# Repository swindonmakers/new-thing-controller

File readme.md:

Universal WIFI Thing Controller for doing stuff around the makerspace. Machine control, data logging, etc etc.

## Features:
 * Wifi (via Pico W)
 * SPI LCD
 * Resistive touch
 * SD card
 * Buttons
 * WS2812B (onboard + header)
 * 2x relay/contactor coil outputs
 * PN532 NFC card reader header
 * Unusued GPIO expansion

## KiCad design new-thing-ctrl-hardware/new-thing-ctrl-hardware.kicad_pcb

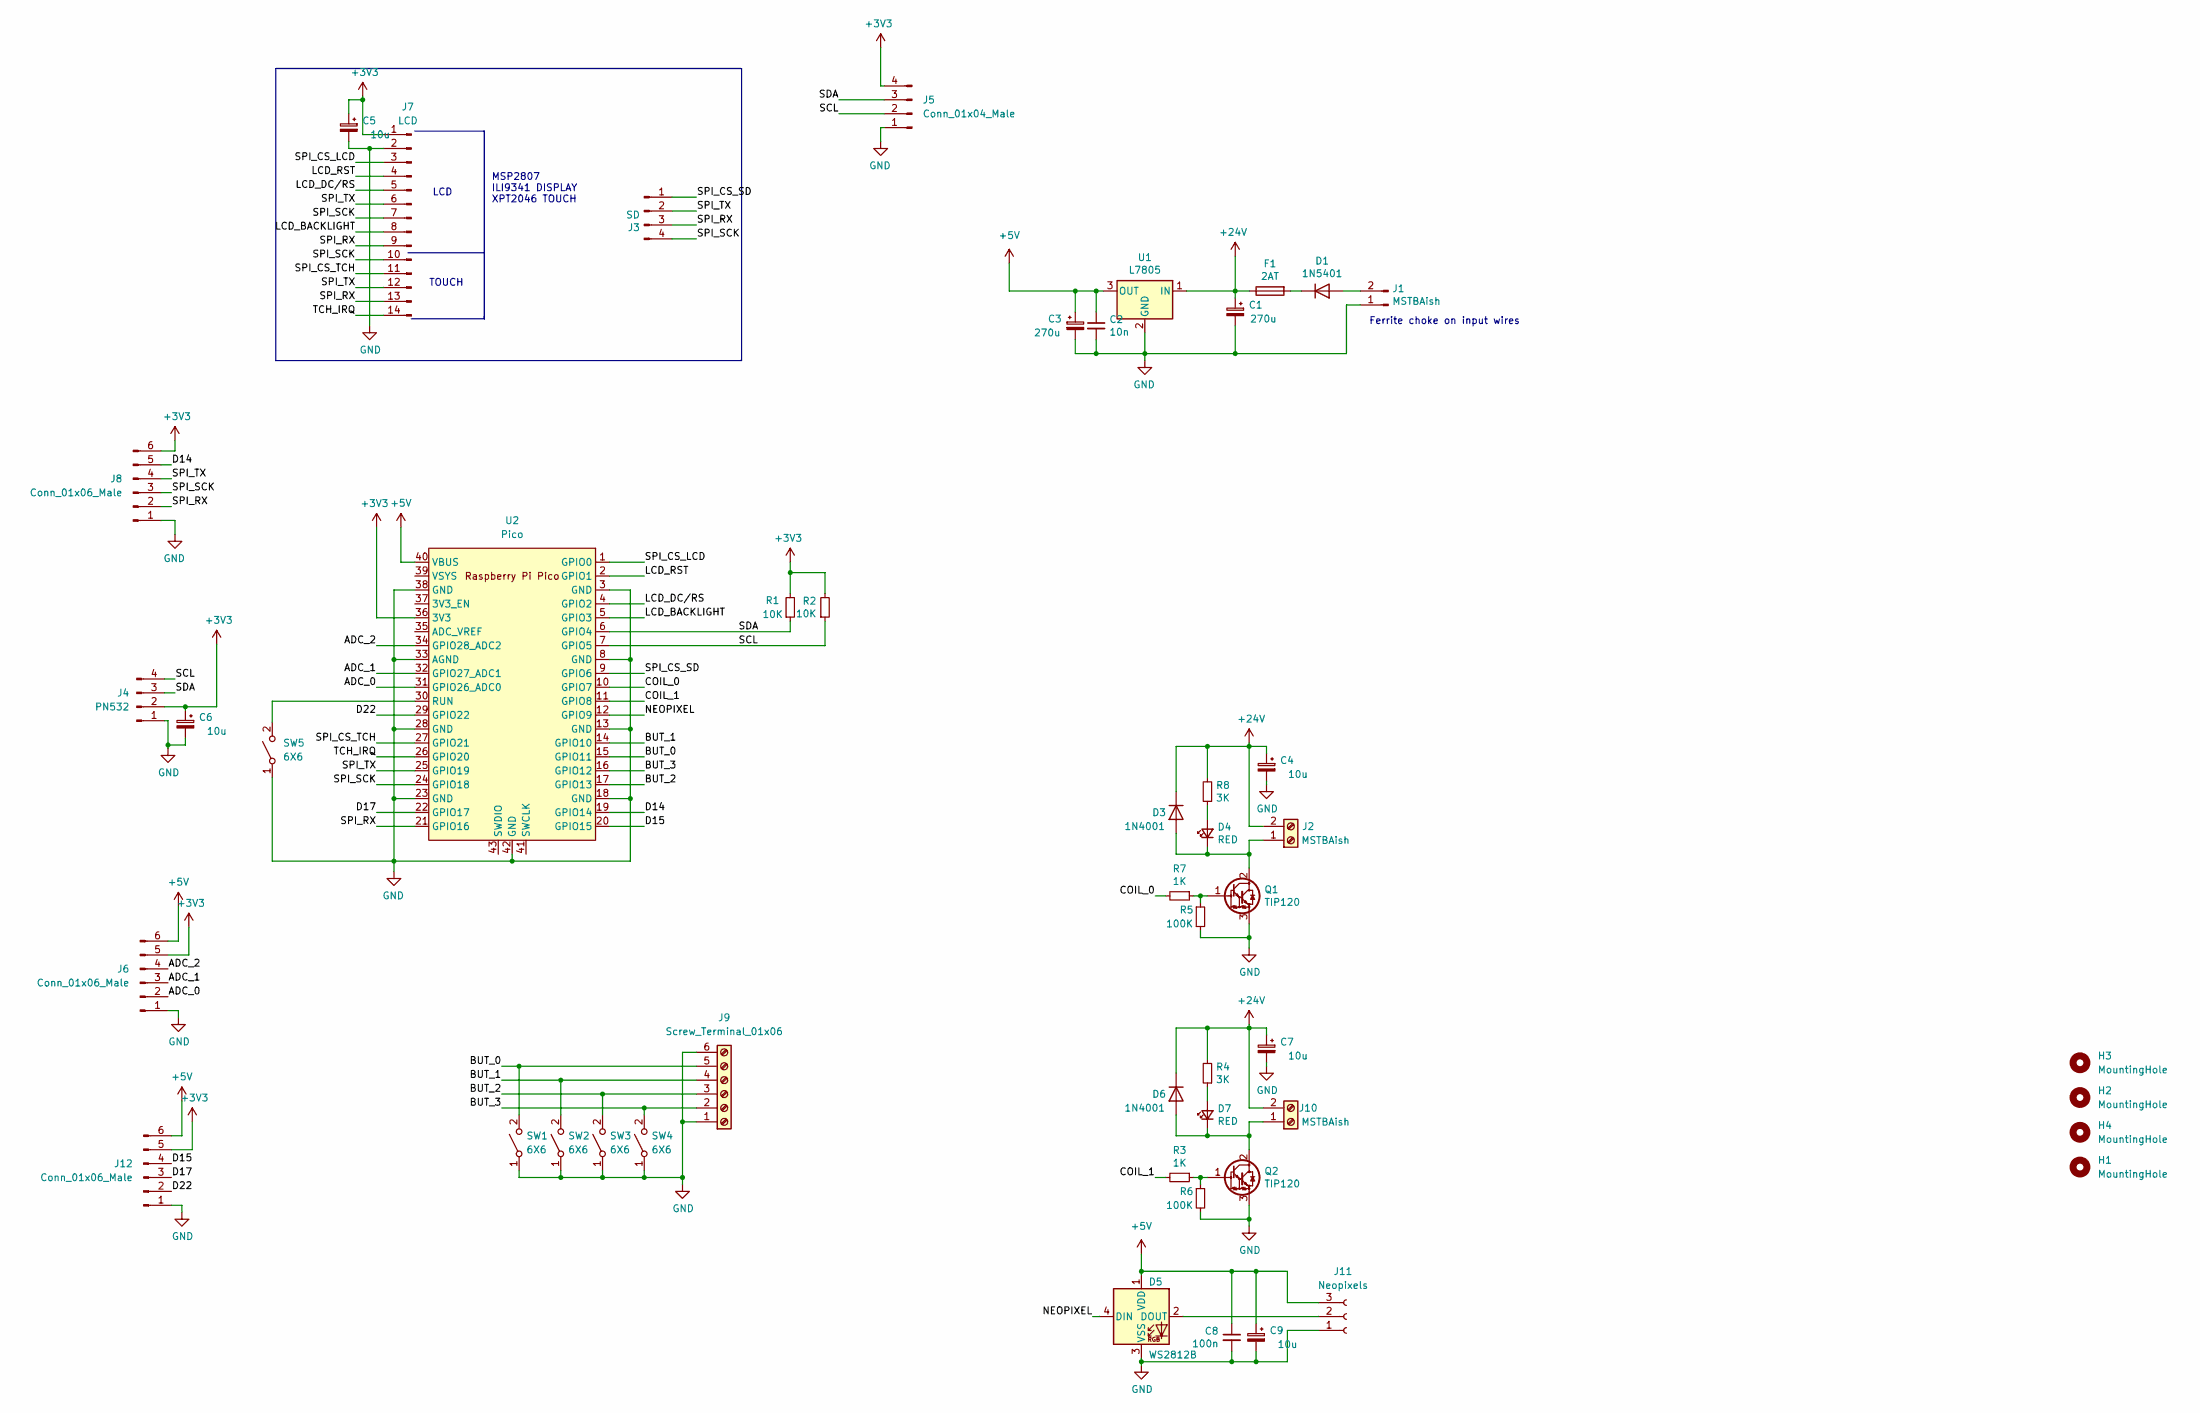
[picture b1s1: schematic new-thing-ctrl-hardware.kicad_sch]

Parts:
C1, C3: 270u; CP_Radial_D10.0mm_P5.00mm
C2: 10n; C_Disc_D7.0mm_W2.5mm_P5.00mm
C4, C5, C6, C7, C9: 10u; CP_Radial_D5.0mm_P2.50mm
C8: 100n; C_Disc_D7.0mm_W2.5mm_P5.00mm
D1: 1N5401; D_DO-201AD_P15.24mm_Horizontal
D3, D6: 1N4001; D_DO-41_SOD81_P10.16mm_Horizontal
D4, D7: RED; LED_D5.0mm
D5: WS2812B; LED_WS2812B_PLCC4_5.0x5.0mm_P3.2mm
F1: 2AT; Fuseholder_Cylinder-5x20mm_Schurter_0031_8201_Horizontal_Op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
H1, H2, H3, H4: MountingHole; MountingHole_3.2mm_M3
J1, J2, J10: MSTBAish; PhoenixContact_MSTBA_2,5_2-G-5,08_1x02_P5.08mm_Horizontal
J3: SD; PinHeader_1x04_P2.54mm_Vertical
J4: PN532; JST_XH_S4B-XH-A_1x04_P2.50mm_Horizontal
J5: Conn_01x04_Male; JST_XH_S4B-XH-A_1x04_P2.50mm_Horizontal
J6, J8, J12: Conn_01x06_Male; JST_XH_S6B-XH-A_1x06_P2.50mm_Horizontal
J7: LCD; PinHeader_1x14_P2.54mm_Vertical
J9: Screw_Terminal_01x06; PhoenixContact_MSTBA_2,5_6-G-5,08_1x06_P5.08mm_Horizontal
J11: Neopixels; JST_XH_S3B-XH-A-1_1x03_P2.50mm_Horizontal
Q1, Q2: TIP120; TO-220-3_Horizontal_TabDown
R1, R2: 10K; R_Axial_DIN0204_L3.6mm_D1.6mm_P7.62mm_Horizontal
R3, R7: 1K; R_Axial_DIN0204_L3.6mm_D1.6mm_P7.62mm_Horizontal
R4, R8: 3K; R_Axial_DIN0204_L3.6mm_D1.6mm_P7.62mm_Horizontal
R5, R6: 100K; R_Axial_DIN0204_L3.6mm_D1.6mm_P7.62mm_Horizontal
SW1, SW2, SW3, SW4: 6X6; SW_PUSH_6mm_H13mm
SW5: 6X6; SW_PUSH_6mm_H4.3mm
U1: L7805; TO-220-3_Horizontal_TabDown
U2: Pico; RPi_Pico_SMD_TH

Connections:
+3V3: C5.1, C6.1, J4.2, J5.4, J6.5, J7.1, J8.6, J12.5, R1.2, R2.2, U2.36 (3V3)
+5V: C2.1, C3.1, C8.1, C9.1, D5.1 (VDD), J6.6, J11.3, J12.6, U1.3 (OUT), U2.40 (VBUS)
+24V: C1.1, C4.1, C7.1, D3.1 (K), D6.1 (K), F1.1, J2.2, J10.2, R4.2, R8.2, U1.1 (IN)
/ADC_0: J6.2, U2.31 (GPIO26_ADC0)
/ADC_1: J6.3, U2.32 (GPIO27_ADC1)
/ADC_2: J6.4, U2.34 (GPIO28_ADC2)
/BUT_0: J9.5, SW1.2 (B), U2.15 (GPIO11)
/BUT_1: J9.4, SW2.2 (B), U2.14 (GPIO10)
/BUT_2: J9.3, SW3.2 (B), U2.17 (GPIO13)
/BUT_3: J9.2, SW4.2 (B), U2.16 (GPIO12)
/COIL_0: R7.2, U2.10 (GPIO7)
/COIL_1: R3.2, U2.11 (GPIO8)
/D14: J8.5, U2.19 (GPIO14)
/D15: J12.4, U2.20 (GPIO15)
/D17: J12.3, U2.22 (GPIO17)
/D22: J12.2, U2.29 (GPIO22)
/LCD_BACKLIGHT: J7.8, U2.5 (GPIO3)
/LCD_DC/RS: J7.5, U2.4 (GPIO2)
/LCD_RST: J7.4, U2.2 (GPIO1)
/NEOPIXEL: D5.4 (DIN), U2.12 (GPIO9)
/SCL: J4.4, J5.2, R2.1, U2.7 (GPIO5)
/SDA: J4.3, J5.3, R1.1, U2.6 (GPIO4)
/SPI_CS_LCD: J7.3, U2.1 (GPIO0)
/SPI_CS_SD: J3.1, U2.9 (GPIO6)
/SPI_CS_TCH: J7.11, U2.27 (GPIO21)
/SPI_RX: J3.3, J7.9, J7.13, J8.2, U2.21 (GPIO16)
/SPI_SCK: J3.4, J7.7, J7.10, J8.3, U2.24 (GPIO18)
/SPI_TX: J3.2, J7.6, J7.12, J8.4, U2.25 (GPIO19)
/TCH_IRQ: J7.14, U2.26 (GPIO20)
GND: C1.2, C2.2, C3.2, C4.2, C5.2, C6.2, C7.2, C8.2, C9.2, D5.3 (VSS), J1.1, J4.1, J5.1, J6.1, J7.2, J8.1, J9.1, J9.6, J11.1, J12.1, Q1.3 (E), Q2.3 (E), R5.2, R6.2, SW1.1 (A), SW2.1 (A), SW3.1 (A), SW4.1 (A), SW5.1 (A), U1.2 (GND), U2.3 (GND), U2.8 (GND), U2.13 (GND), U2.18 (GND), U2.23 (GND), U2.28 (GND), U2.33 (AGND), U2.38 (GND), U2.42 (GND)
unnamed: D1.1 (K), F1.2
unnamed: D1.2 (A), J1.2
unnamed: D3.2 (A), D4.1 (K), J2.1, Q1.2 (C)
unnamed: D4.2 (A), R8.1
unnamed: D5.2 (DOUT), J11.2
unnamed: D6.2 (A), D7.1 (K), J10.1, Q2.2 (C)
unnamed: D7.2 (A), R4.1
unnamed: Q1.1 (B), R5.1, R7.1
unnamed: Q2.1 (B), R3.1, R6.1
unnamed: SW5.2 (B), U2.30 (RUN)

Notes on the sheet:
LCD
TOUCH
MSP2807 ILI9341 DISPLAY XPT2046 TOUCH
Ferrite choke on input wires

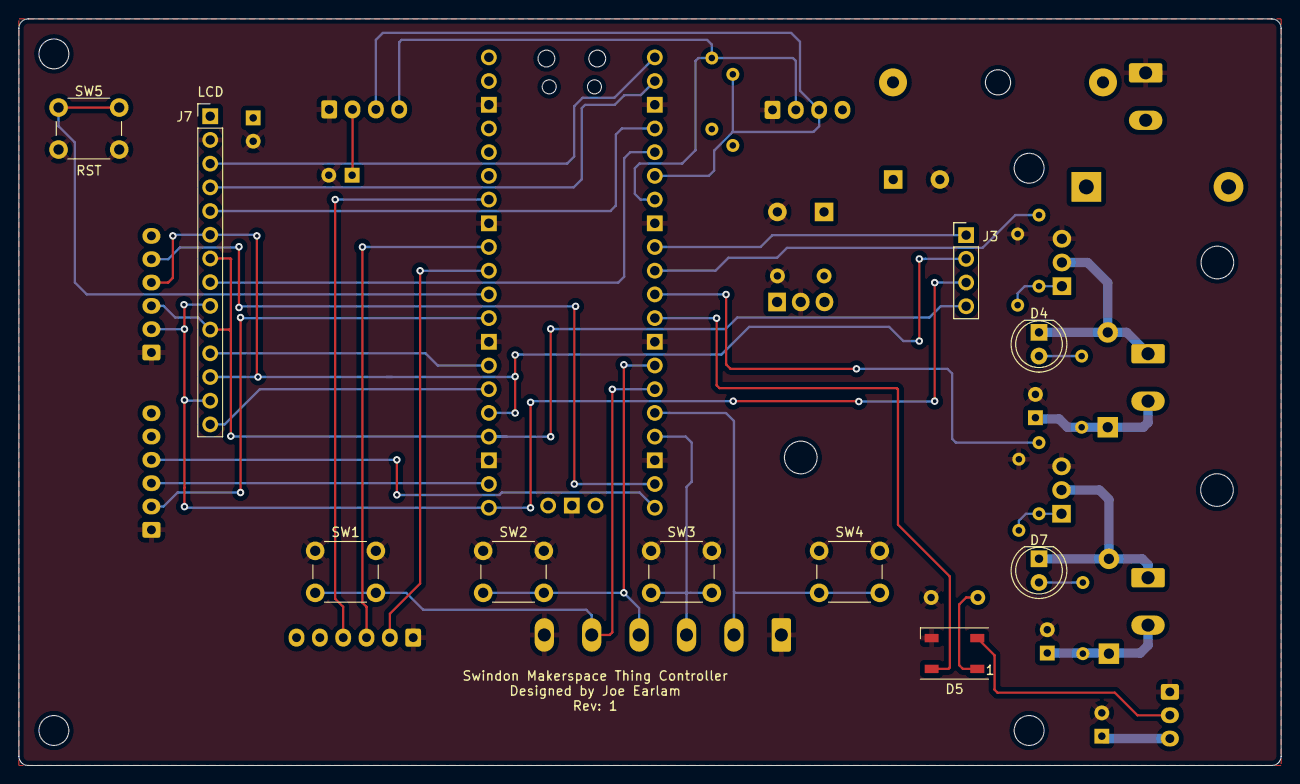
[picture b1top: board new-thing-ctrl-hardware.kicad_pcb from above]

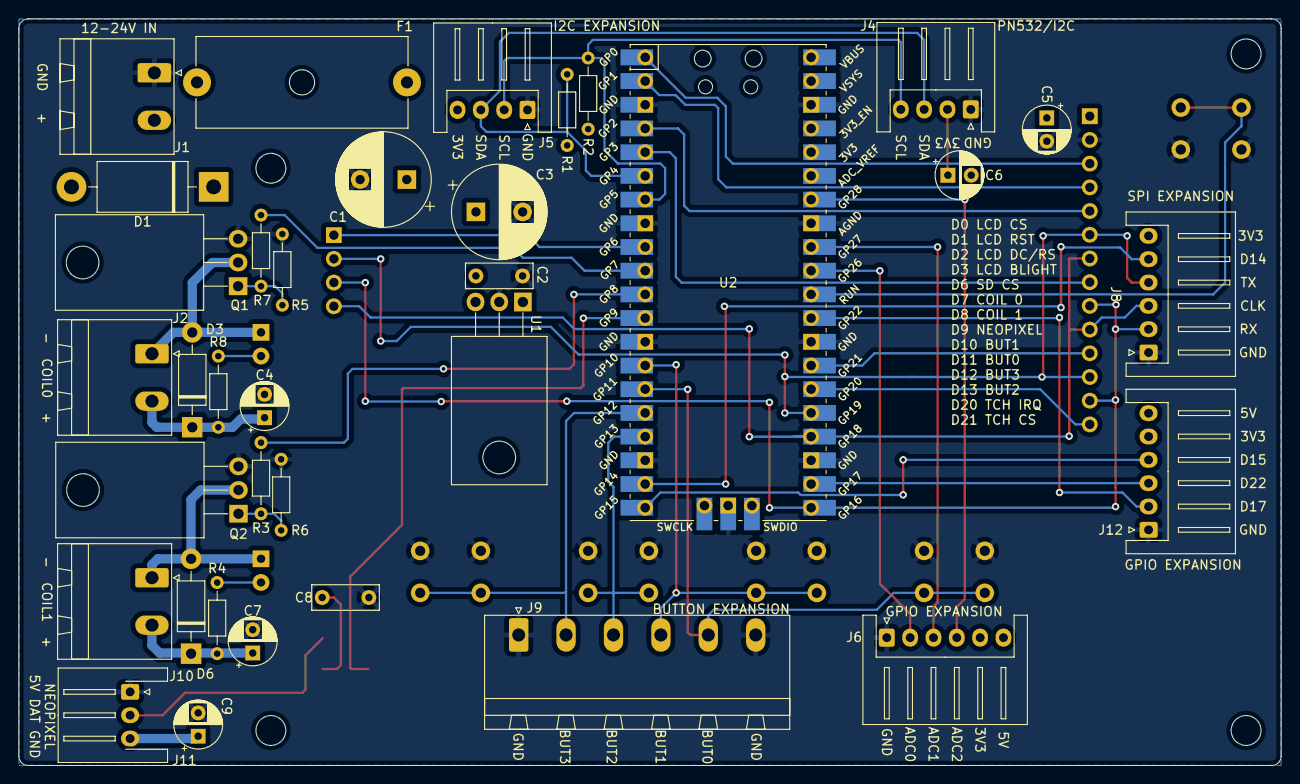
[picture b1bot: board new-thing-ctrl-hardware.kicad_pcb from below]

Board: 4 copper layers, 135.2 x 80.0 mm, 49 parts (35 on the bottom side), 40 nets.

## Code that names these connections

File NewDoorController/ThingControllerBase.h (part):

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#define LCD_DC 2
#define LCD_MOSI 19
#define LCD_CLK 18
#define LCD_RST 1
#define LCD_MISO 16
#define LCD_BACKLIGHT 3
#define BTN0 11
#define BTN1 10
#define BTN2 13
#define BTN3 12
#define NEOPIXEL 9

#if ThingControllerBoardRev == 1
#define I2C_IRQ 14
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#define PN532_READ_TIMEOUT 50     // milliseconds

#ifndef NUM_LEDS
#define NUM_LEDS 24  //Number of LEDs in neopixel strip (built in one should be bypassed)
#endif

//NeoPixel Colour references
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  void initLcd() {
    lcd.begin();
    lcd.setRotation(3);                 //set screen to right way around
    pinMode(LCD_BACKLIGHT, OUTPUT);     //backlight
    digitalWrite(LCD_BACKLIGHT, HIGH);  //turn backlight on (otherwise you cant see anything)
    //clear screen probably not needed
    lcd.fillScreen(ILI9341_BLACK);
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
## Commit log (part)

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2022-12-14 routed
2022-12-29 ready for review and manufacture
2022-12-30 changed some connector footprints, added reset button
2023-01-25 implemented SPI display
2023-02-07 LCD + taskscheduler arduino test code
2023-04-28 Door access running on thing controller
    To replace existing door controller on new thing controller hardware using a pi pico
2023-04-30 Added wired support
    Ethernet connection now also added and initial testing done
    Improved wifi recovery when connection is lost
    Todo: turn Thing controller base to library
    Todo: reduce duplicate code across the wifi and wired versions
2023-07-07 First attempt ready for use
    ThingControllerBase is now a library with wired and wireless modes built in and controlled by defines
    Code is ready for initial use
2023-07-07 reverted personal network settings
    accidentlay checked in wrong network settings
2024-01-31 Initial Door controller commit
    Door controller, includes thing controller.h which should be used by all controllers in the future
2024-03-05 pinout update + i2c recovery
    updated pinout to match real world
    added i2c crash recovery to see if that fixes the door going unresponsive
2024-04-10 Improved ethernet stability
    Added reset of ethernet controller on boot, controller sometimes fails to wake up correctly after power cut, this should help address that be hard reseting after the power has come back before initia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
2024-08-26 Standard thing controller added
    Standard thing controller is for most tools. You need to edit the tool name, UUID, and network settings in data folder to connect correctly
2025-03-31 Tag Assigner
    Added tag assigner code, requires config and Netwrok files in standard thing controller
2025-04-10 Standard Thing Controller V1.1 OTA update
    Added ability for ATO updates
    Requires New config file update with Admin password (this still has to be done via usb for now)
2025-07-04 Prep for Door controller to handle parking
    Prep for Door controller to handle parking and a few minor fixes to other controllers
2025-07-04 Added verbosity of debug messages
    an initial attempt to help understand why the thing controllers are randomly failing to parse jsons sent from the server
2025-07-05 Standard Thing Controller V1.2
    Added additional debuging modes
    When signed out Holding Induct for 5 seconds enters debug mode - displays basic info and clears cache
    While in this state pressing tool-on/off toggles debug verbosity levels
    - Normal - Normal messages appear
    - High - More debug messages appear on screen
    - Hight + Server - More debug messages appear and sends these msgs to the server for logs
2025-07-20 Initial changes to door controller to support car parking
    Initial changes to door controller to support car parking
2025-07-23 Continued improvement to door controller
    getting close to final version for door parking cars for members
2026-01-01 Door can now beep with messages on standard door access
    With tier changes we now want the door to beep at people so they read messages, this update adds that feature
